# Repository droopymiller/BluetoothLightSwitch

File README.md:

# BluetoothLightSwitch
This project includes code and a schematic to make a bluetooth opperated light switch.
It accomplishes this using the Arduino Nano and HM-10

Because the HM-10 I had was actually a CC41-A, the "BRK" pin doesn't exist.
This lead me to connect the bluetooth module's VCC to an output on the Arduino so that it could be power cycled in order to disconnect clients

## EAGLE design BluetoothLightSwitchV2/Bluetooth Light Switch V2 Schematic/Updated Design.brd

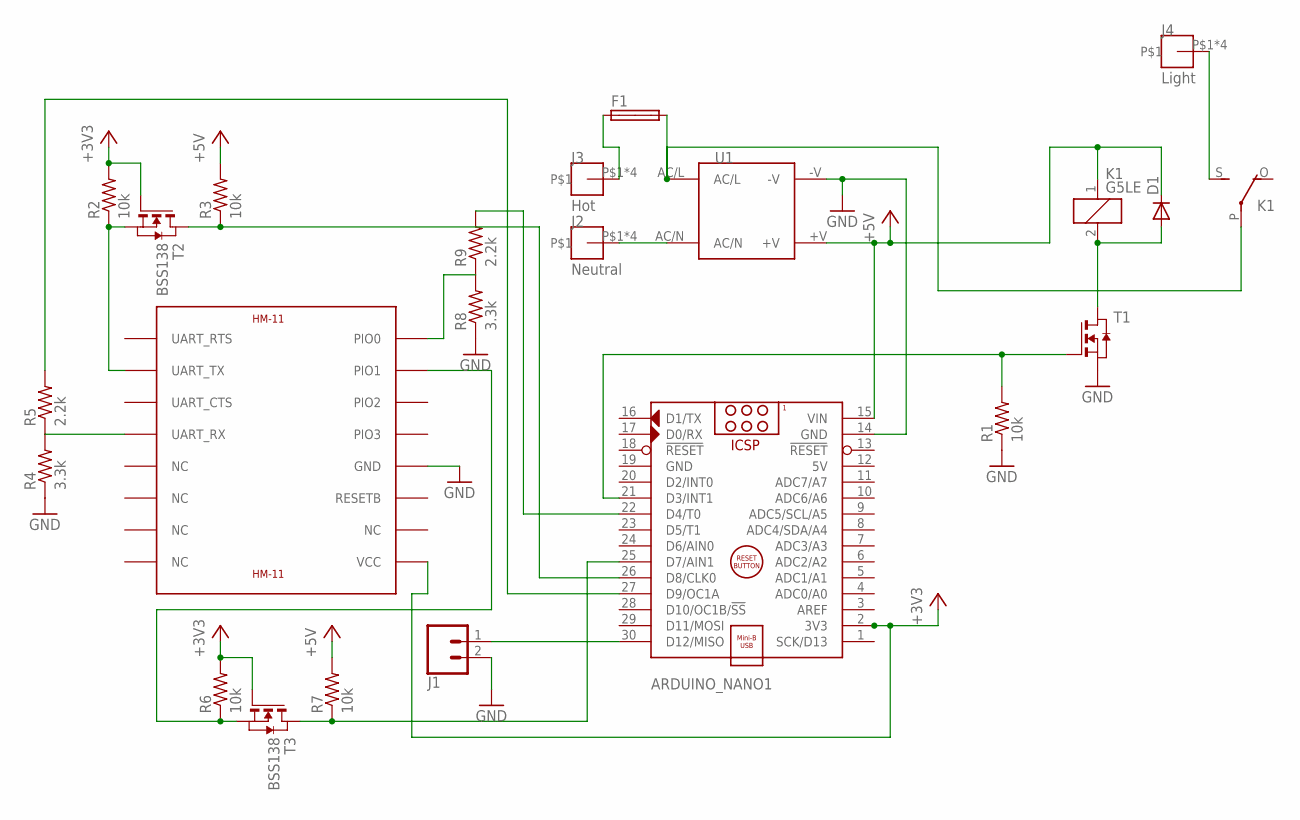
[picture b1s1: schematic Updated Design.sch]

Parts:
ARDUINO_NANO1: ARDUINO_NANO
D1: DIODE-SOD80C; SOD80C
F1: SHK20L
J1: CONN_025MM; SCREWTERMINAL-5MM-2
J2: Neutral; 7700
J3: Hot; 7700
J4: Light; 7700
K1: G5LE
R1, R2, R3, R6, R7: 10k; R0603
R4, R8: 3.3k; R0603
R5, R9: 2.2k; R0603
T1: NMOSSOT23; SOT-23
T2, T3: BSS138; SOT-23
U1: IRM-05-5; IRM-05
U$1: HM-11

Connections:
5V: ARDUINO_NANO1.12 (5V)
+3V3: ARDUINO_NANO1.2 (3V3), R2.2, R6.2, T2.3 (G), T3.3 (G), U$1.VCC
+5V: ARDUINO_NANO1.15 (VIN), D1.C, K1.1, R3.2, R7.2, U1.+V
GND: ARDUINO_NANO1.14 (GND), ARDUINO_NANO1.19 (GND), J1.2, U1.-V, U$1.GND
unnamed: ARDUINO_NANO1.30 (D12/MISO), J1.1
unnamed: R4.2, U$1.UART_RX
unnamed: ARDUINO_NANO1.21 (D3/INT1), T1.3 (G)
unnamed: F1.2A, K1.P, U1.AC/L
unnamed: J2.P$1, J2.P$2, J2.P$3, J2.P$4, U1.AC/N
unnamed: J4.P$1, J4.P$2, J4.P$3, J4.P$4, K1.S
unnamed: ARDUINO_NANO1.27 (D9/OC1A), R5.2
unnamed: D1.A, K1.2, T1.1 (D)
unnamed: R2.1, T2.2 (S), U$1.UART_TX
unnamed: ARDUINO_NANO1.26 (D8/CLK0), R3.1, T2.1 (D)
unnamed: R6.1, T3.2 (S), U$1.PIO1
unnamed: ARDUINO_NANO1.25 (D7/AIN1), R7.1, T3.1 (D)
unnamed: ARDUINO_NANO1.22 (D4/T0), R9.2
unnamed: R8.2, U$1.PIO0
unnamed: F1.1A, J3.P$1, J3.P$2, J3.P$3, J3.P$4

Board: 2 copper layers, 22 parts (0 on the bottom side), 18 nets, no tracks yet.

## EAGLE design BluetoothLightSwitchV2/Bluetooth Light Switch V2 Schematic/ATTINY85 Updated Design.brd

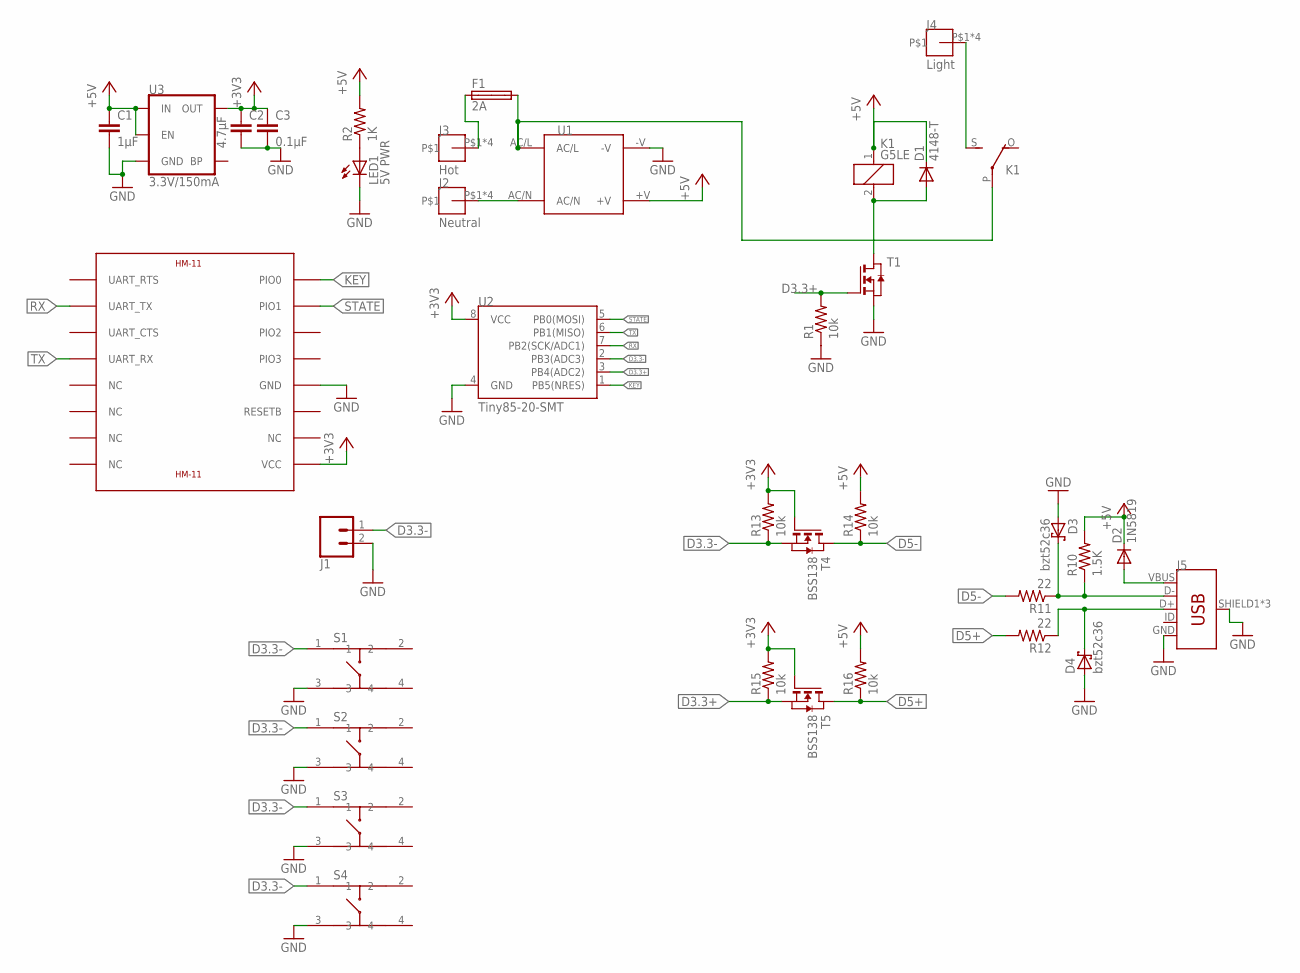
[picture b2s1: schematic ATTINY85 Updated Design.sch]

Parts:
C1: 1µF; C0603K
C2: 4.7µF; C0603K
C3: 0.1µF; C0603K
D1: 4148-T; SOD80C
D2: 1N5819; SOD323-R
D3, D4: bzt52c36; SOD323_ST
F1: 2A; SHK20L
J1: CONN_025MM; SCREWTERMINAL-5MM-2
J2: Neutral; 7700
J3: Hot; 7700
J4: Light; 7700
J5: USB_MICRO-B_FEMALE-SMT; USB-B-MICRO-SMD
K1: G5LE
LED1: 5V PWR; CHIPLED_0603
R1, R13, R14, R15, R16: 10k; R0603
R2: 1K; R0603
R10: 1.5K; R0603
R11, R12: 22; R0603
S1, S2, S3, S4: PTS645S_SMTR92; SMT
T1: NMOSSOT23; SOT-23
T4, T5: BSS138; SOT-23
U1: IRM-05-5; IRM-05
U2: Tiny85-20-SMT; SO08-EIAJ_MCU
U3: 3.3V/150mA; SOT23-5
U$1: HM-11

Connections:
+3V3: C2.1, C3.1, R13.2, R15.2, T4.3 (G), T5.3 (G), U2.8 (VCC), U3.5 (OUT), U$1.VCC
+5V: C1.1, D1.C, D2.C, K1.1, R2.2, R10.2, R14.2, R16.2, U1.+V, U3.1 (IN), U3.3 (EN)
D3.3+: R1.2, R15.1, T1.3 (G), T5.2 (S), U2.3 (PB4(ADC2))
D3.3-: J1.1, R13.1, S1.1, S2.1, S3.1, S4.1, T4.2 (S), U2.2 (PB3(ADC3))
D5+: R12.2, R16.1, T5.1 (D)
D5-: R11.2, R14.1, T4.1 (D)
GND: C1.2, C2.2, C3.2, D3.A, D4.A, J1.2, J5.GND, J5.SHIELD1 (SHIELD), J5.SHIELD2 (SHIELD), J5.SHIELD3 (SHIELD), LED1.C, R1.1, S1.3, S2.3, S3.3, S4.3, T1.2 (S), U1.-V, U2.4 (GND), U3.2 (GND), U$1.GND
HOT: F1.1A, J3.P$1, J3.P$2, J3.P$3, J3.P$4
KEY: U2.1 (PB5(NRES)), U$1.PIO0
LIGHT: J4.P$1, J4.P$2, J4.P$3, J4.P$4, K1.S
unnamed: LED1.A, R2.1
unnamed: F1.2A, K1.P, U1.AC/L
unnamed: D1.A, K1.2, T1.1 (D)
unnamed: D2.A, J5.VBUS
unnamed: D3.C, J5.D-, R10.1, R11.1
unnamed: D4.C, J5.D+, R12.1
NEUTRAL: J2.P$1, J2.P$2, J2.P$3, J2.P$4, U1.AC/N
RX: U2.7 (PB2(SCK/ADC1)), U$1.UART_TX
STATE: U2.5 (PB0(MOSI)), U$1.PIO1
TX: U2.6 (PB1(MISO)), U$1.UART_RX

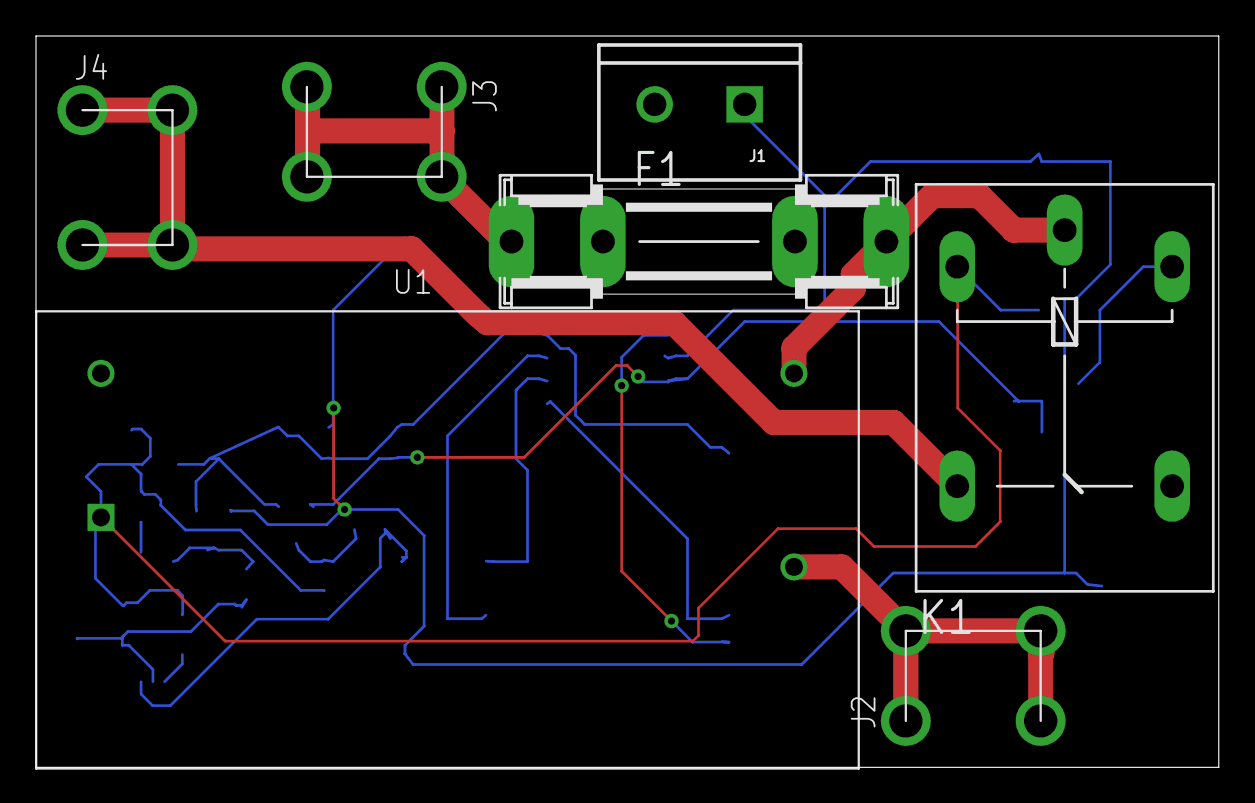
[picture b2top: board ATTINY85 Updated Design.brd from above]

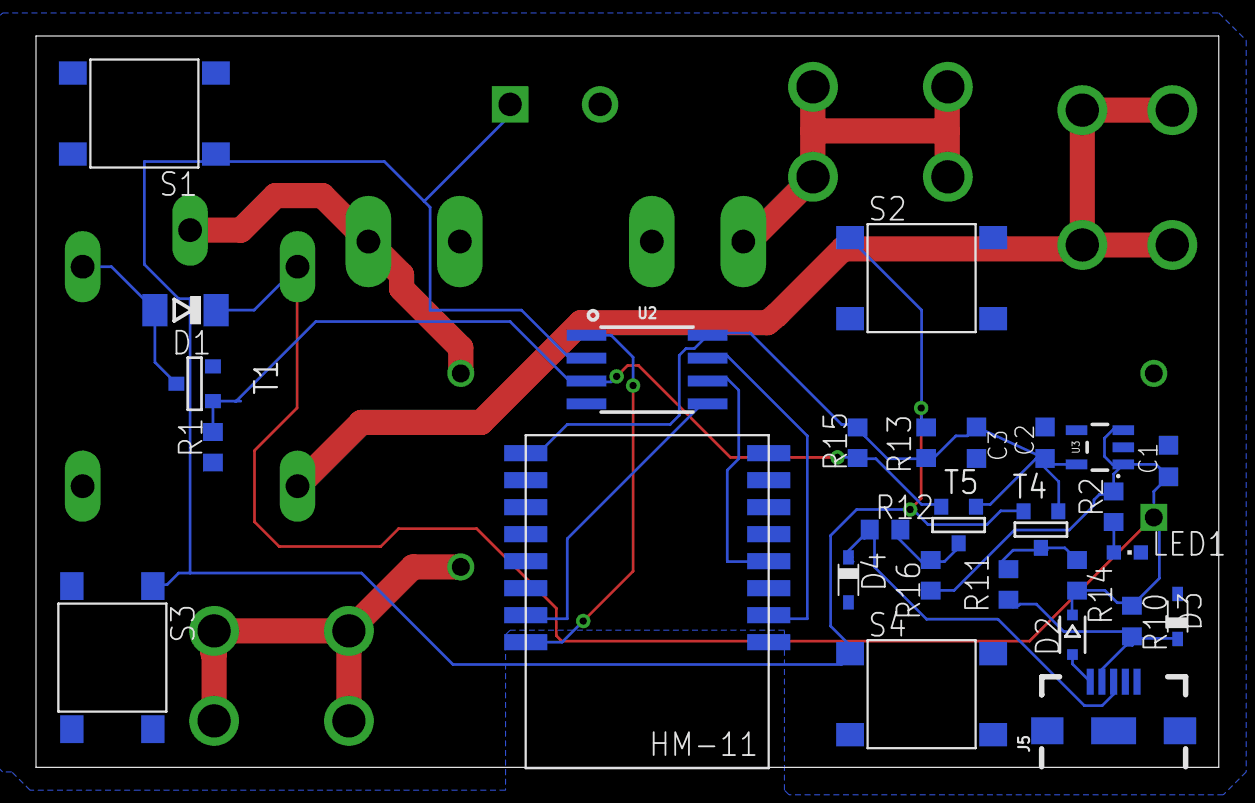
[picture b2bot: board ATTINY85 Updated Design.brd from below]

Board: 2 copper layers, 65.7 x 40.6 mm, 35 parts (28 on the bottom side), 20 nets.

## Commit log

2017-10-07 Start of Arduino file, Added .gitignore to ignore mac files
2017-10-07 Initial declaration of variables and some basic functions
2017-10-07 Bluetooth functionality is complete, no switch functionality
2017-10-07 Added schematic image
2017-10-08 Switch is functional
2017-10-15 Fixed debounce function Added disconnect function (disconnect client from HM-10 after receiving instruction by power cycling HM-10) Added debug mode (Client is not automatically disconnected)
2017-10-15 Added Fritzing Schematic, removed hand drawn schematic
2017-10-15 Removed "Part 1", "Part 2" labels
2017-10-15 Create LICENSE
2017-10-16 Fixed bugs
2018-01-03 Separated Original Design (V1) from Updated Design (V2)
2018-01-03 Updated Original Code to Accomodate Attiny85 | No Testing -Updated Pins -Removed USB Serial Interfacing
2018-04-18 Fixed error
2019-02-02 Copied V1 code to V3 to start new project

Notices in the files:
parts and their libraries:
SparkFun-Connectors: Licensing: Creative Commons ShareAlike 4.0 International - https://creativecommons.org/licenses/by-sa/4.0
